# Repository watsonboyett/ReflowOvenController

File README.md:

ThermoBot
====================

A temperature controller module that's designed to follow a pre-programmed temperature profile. The target application for this project is to be used a controller for a reflow oven.

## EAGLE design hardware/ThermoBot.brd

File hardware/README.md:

## Revision History

### v1A

* Initial design

### v1B

* Renamed to ThermoBot (formerly Tempatroller)
* Replaced 2.5mm terminal connectors with 5mm and moved them to allow for easier access
* Replaced AC-DC power supply with smaller footprint
* Replace TRIAC with SSR (for higher current rating)
* Added power and heartbeat status LEDs
* Added terminal header for powering a heatsink fan
* Improved layout

### Not-Yet-Implemented Changes

* provide safety mechanism for using external SSR (ensure that internal SSR isn't active)
** perhaps a jumper for setting internal/external SSR
* provide breakout connections for unused pins (for switches, LCD panel, or other sensors)
* Add mounting holes that match with Arduino Uno r3 holes
* Add fiducials to allow for pick and place alignment
* Add "Risk of Shock" warnings to MAINS partition (both sides)

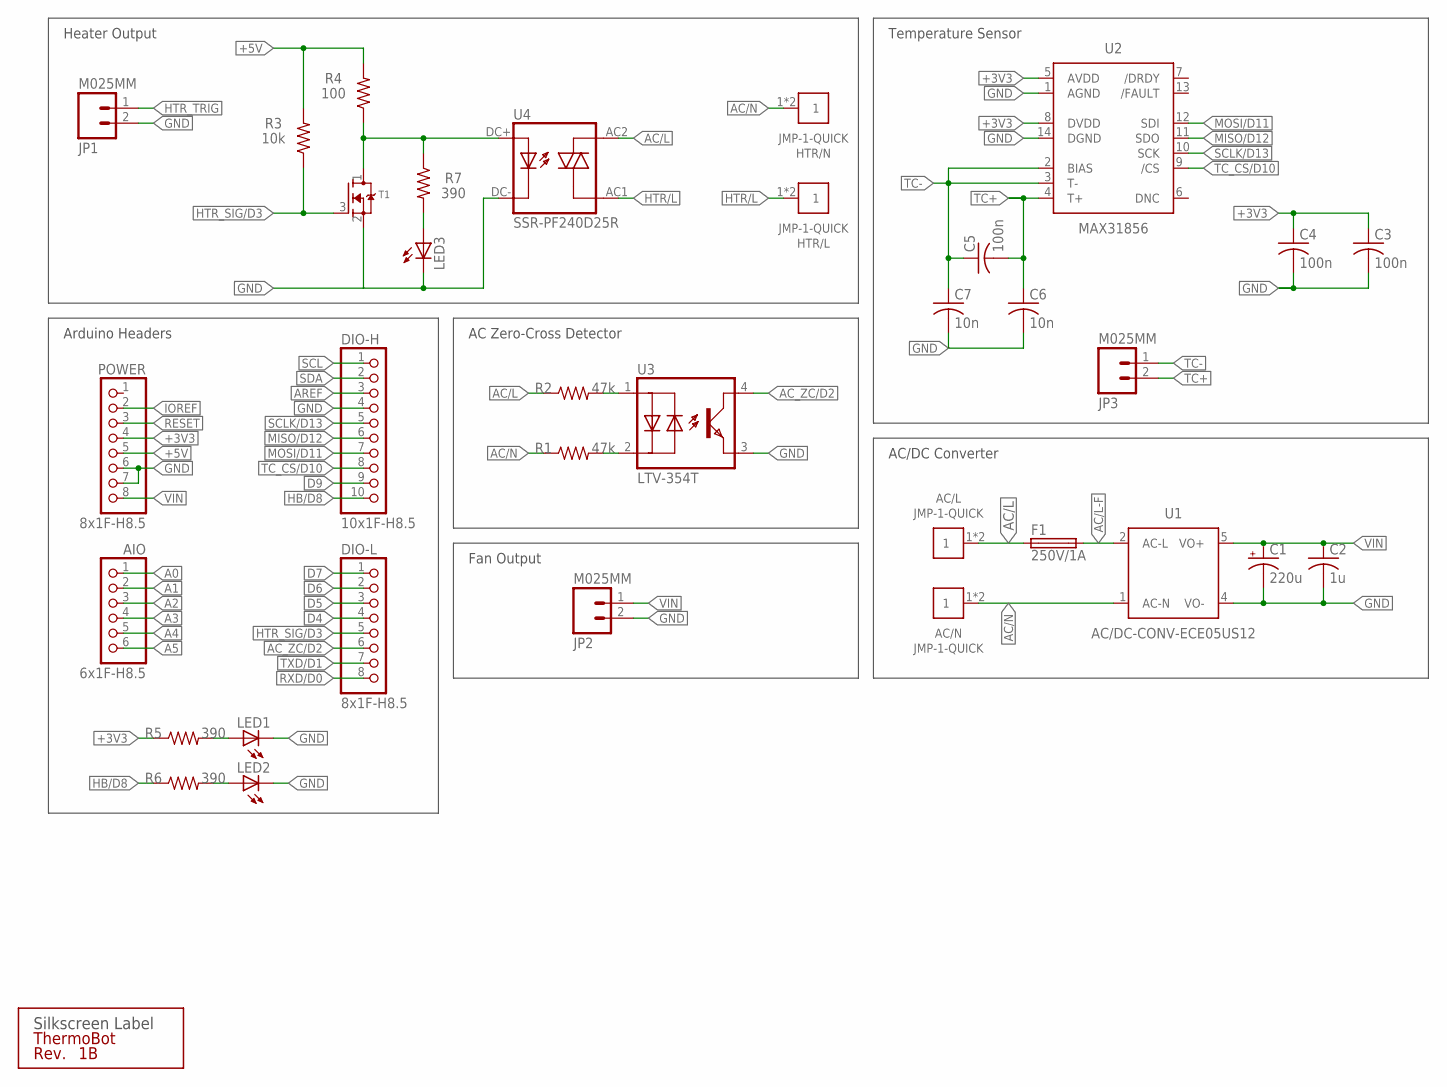
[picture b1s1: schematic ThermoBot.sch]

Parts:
AC/L: JMP-1-QUICK; QUICK-1
AC/N: JMP-1-QUICK; QUICK-1
AIO: 6x1F-H8.5; 1X06
C1: 220u; 153CLV-1014
C2: 1u; C0805
C3, C4, C5: 100n; C0805
C6, C7: 10n; C0805
DIO-H: 10x1F-H8.5; 1X10
DIO-L: 8x1F-H8.5; 1X08
F1: 250V/1A; 2SMD-2410; MPN 0454001.MR
HTR/L: JMP-1-QUICK; QUICK-1
HTR/N: JMP-1-QUICK; QUICK-1
JP1, JP2, JP3: M025MM; SCREWTERMINAL-5MM-2
LED1, LED2, LED3: LEDCHIP-LED0805; CHIP-LED0805
POWER: 8x1F-H8.5; 1X08
R1, R2: 47k; R1206
R3: 10k; R0805
R4: 100; R0805
R5, R6, R7: 390; R0805
T1: MOSFET-N-SOT23; SOT-23
U1: AC/DC-CONV-ECE05US12; ECE05
U2: MAX31856; TSSOP14
U3: LTV-354T; SOP-4
U4: SSR-PF240D25R; SIP-4
U$1: SILK_QC

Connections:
+3V3: C3.1, C4.1, POWER.4, R5.1, U2.5 (AVDD), U2.8 (DVDD)
+5V: POWER.5, R3.2, R4.2
A0: AIO.1
A1: AIO.2
A2: AIO.3
A3: AIO.4
A4: AIO.5
A5: AIO.6
AC/L: AC/L.1, AC/L.2, F1.P$1 (1), R2.1, U4.AC2 (A2)
AC/L-F: F1.P$2 (2), U1.2 (AC-L)
AC/N: AC/N.1, AC/N.2, HTR/N.1, HTR/N.2, R1.1, U1.1 (AC-N)
AC_ZC/D2: DIO-L.6, U3.4 (COL)
AREF: DIO-H.3
D4: DIO-L.4
D5: DIO-L.3
D6: DIO-L.2
D7: DIO-L.1
D9: DIO-H.9
GND: C1.-, C2.2, C3.2, C4.2, C6.2, C7.2, DIO-H.4, JP1.2, JP2.2, LED1.C, LED2.C, LED3.C, POWER.6, POWER.7, T1.2 (S1), U1.4 (VO-), U2.1 (AGND), U2.14 (DGND), U3.3 (EMIT), U4.DC- (C)
HB/D8: DIO-H.10, R6.1
HTR/L: HTR/L.1, HTR/L.2, U4.AC1 (A1)
HTR_SIG/D3: DIO-L.5, R3.1, T1.3 (G1)
HTR_TRIG: JP1.1, R4.1, R7.1, T1.1 (D1), U4.DC+ (A)
IOREF: POWER.2
MISO/D12: DIO-H.6, U2.11 (SDO)
MOSI/D11: DIO-H.7, U2.12 (SDI)
unnamed: R1.2, U3.2 (C)
unnamed: R2.2, U3.1 (A)
unnamed: LED3.A, R7.2
unnamed: LED1.A, R5.2
unnamed: LED2.A, R6.2
RESET: POWER.3
RXD/D0: DIO-L.8
SCL: DIO-H.1
SCLK/D13: DIO-H.5, U2.10 (SCK)
SDA: DIO-H.2
TC+: C5.2, C6.1, JP3.2, U2.4 (T+)
TC-: C5.1, C7.1, JP3.1, U2.2 (BIAS), U2.3 (T-)
TC_CS/D10: DIO-H.8, U2.9 (/CS)
TXD/D1: DIO-L.7
VIN: C1.+, C2.1, JP2.1, POWER.8, U1.5 (VO+)

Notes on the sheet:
Arduino Headers
Temperature Sensor
Heater Output
AC/DC Converter
AC Zero-Cross Detector
Fan Output

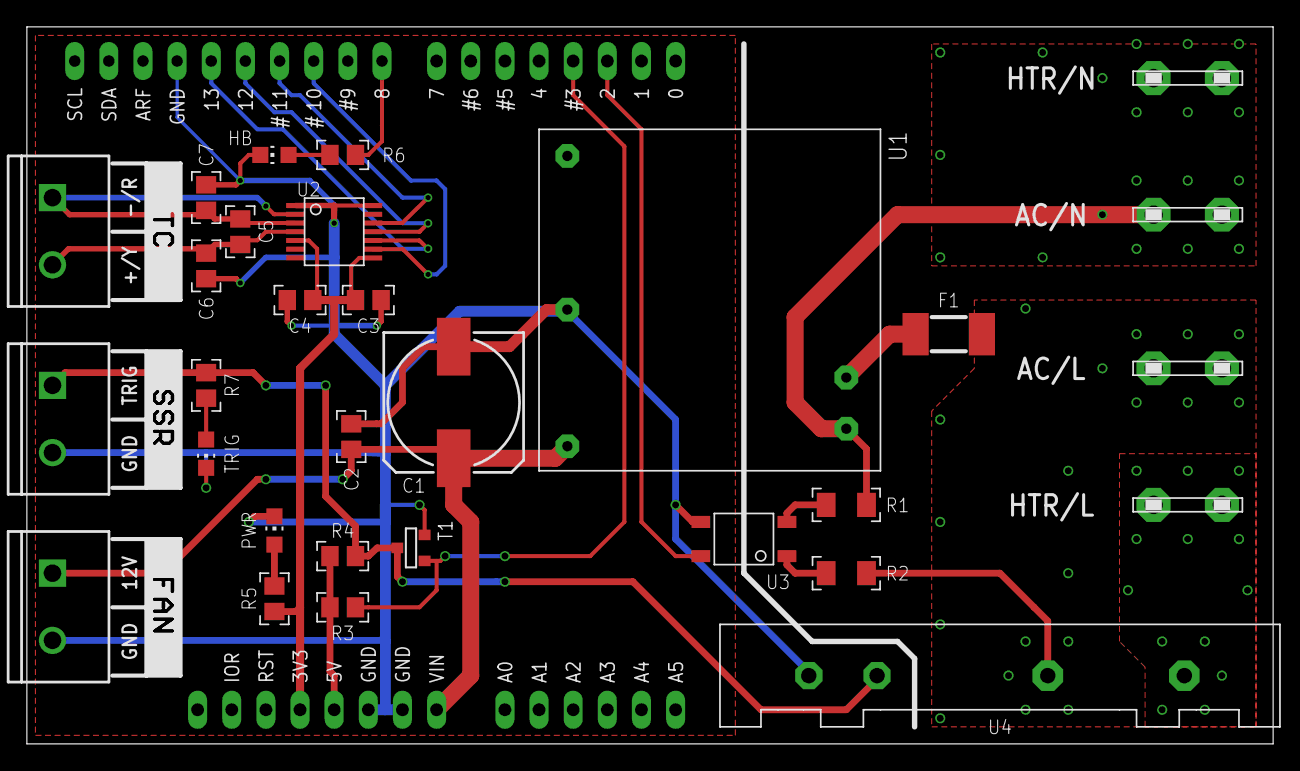
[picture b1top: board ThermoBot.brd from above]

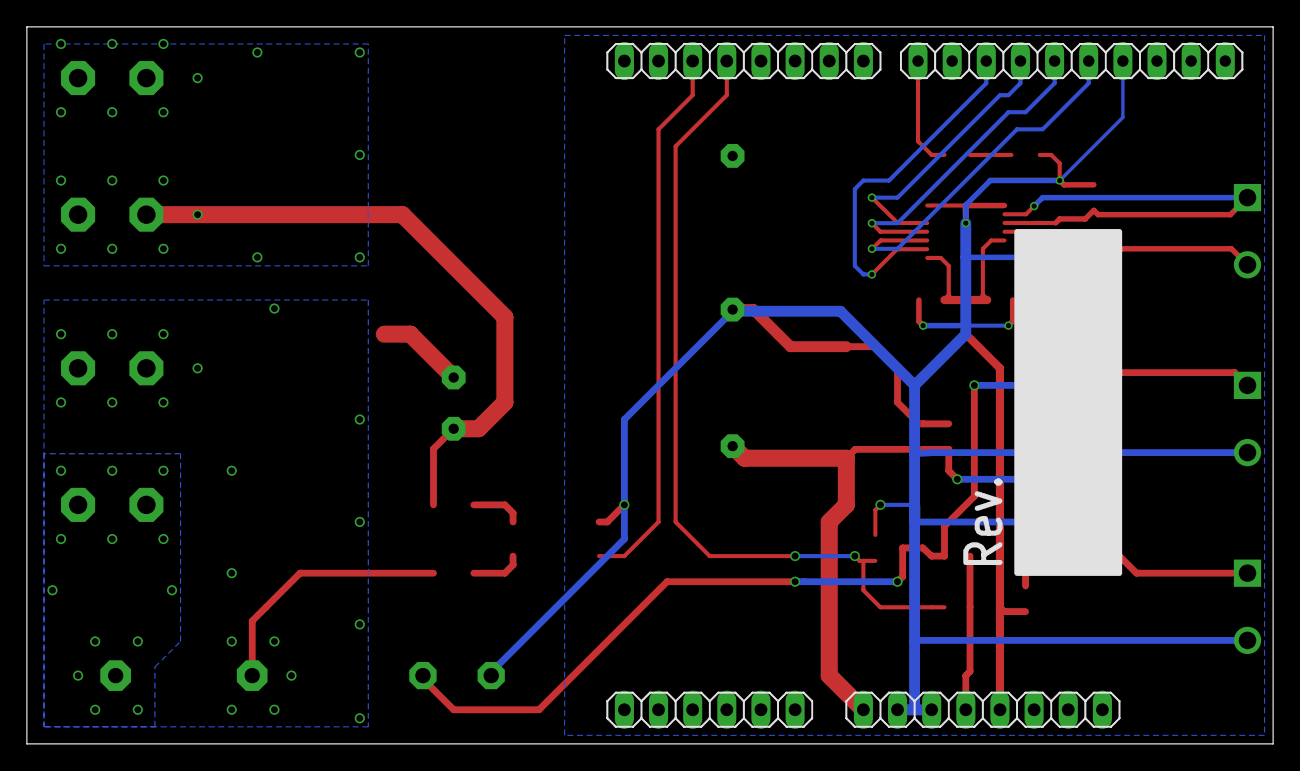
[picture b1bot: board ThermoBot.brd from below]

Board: 2 copper layers, 92.7 x 53.3 mm, 38 parts (5 on the bottom side), 23 nets.

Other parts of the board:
U$2: SILK_FAN
U$3: SILK_SSR
U$4: SILK_TC

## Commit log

2017-06-10 Initial commit of existing project.
2017-06-10 Removed spurious BOM file
2017-06-10 Fixed BOM parts that used Digi-Reel packaging instead of cut-tape
2017-06-13 Added existing firmware code.
2017-07-02 Updated firmware to use MAX31856 thermocouple converter.
2017-07-02 Added notes on Rev. A hardware design (mostly what needs to be fixed in Rev. B)
2017-07-10 Added elapsed time to console output.
2017-07-10 Improved mechanical layout. Added status leds.
2017-07-10 Packed all parts into local project library. Renamed project files.
2017-12-08 Renamed to ThermoBot
2017-12-08 Refactored code into separate modules. Added support for temperature setpoint profiles.
2017-12-09 Started hardware revisions for v1B
2017-12-10 Finalized v1B design and generated MFG docs
2017-12-19 Updated TC silkscreen labels. Fixed via silkscreen mask. Regenerated archive file.

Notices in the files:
hardware/ThermoBot.sch:
CONTACT_ADDRESS: Licensed under CC-BY-SA
CONTACT_PHONE: (Creative Commons, Attribution + Share Alike)
